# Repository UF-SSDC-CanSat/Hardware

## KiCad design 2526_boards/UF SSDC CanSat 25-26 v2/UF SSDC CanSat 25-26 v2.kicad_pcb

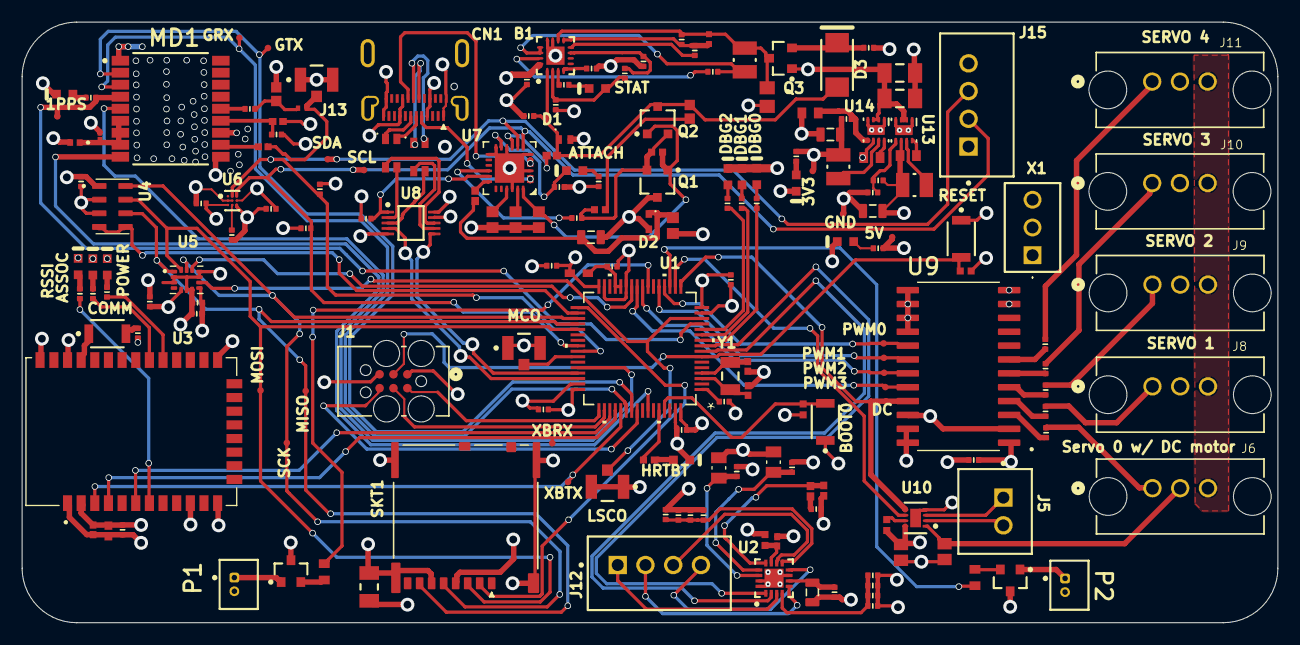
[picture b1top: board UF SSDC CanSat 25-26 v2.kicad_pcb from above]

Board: 4 copper layers, 115.0 x 55.0 mm, 170 parts (0 on the bottom side), 140 nets.

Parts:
B1: BQ25306RTER; QFN50P300X300X80_HS-17N
C1, C7, C8, C9, C14, C16, C18, C19, C21, C27, C30: Capacitor 100nF +/-20% 50V 0402; CAPC0402(1005)60_L
C2, C5, C29: GCM1555C1H9R0BA16D; CAPC1005X06N
C3: Capacitor 1 uF +/- 10% 6.3 V 1005; CAPC1005X55X25ML5T10
C4, C40: Capacitor 10µF +/-40% 6.3V 0402; CAPC0402(1005)60_L
C6: GRM0335C1H560JA01D; CAPC0603X03N
C12, C22: Capacitor 100 nF +/-10% 50 V 0603; CAPC1608X90X40NL10T20
C13: CL05C101JB5NNNC; CAPC1005X06N
C15, C20, C36, C37, C48: Capacitor 2,2µF +/-20% 10V 0402; CAPC0402(1005)60_L
C17, C50: Capacitor 10nF +/-20% 50V 0402; CAPC0402(1005)60_L
C23, C24, C25, C26: Capacitor 1uF +/- 10% 16V 0603; CAPC1608X90X35ML15T15
C28, C46: Capacitor 100 nF +/-10% 50 V 0805; CAPC2013X95X50LL10T25
C31, C33: Capacitor 10 uF +/- 10% 16 V 1206; CAPC3216X180X50NL20T25
C32, C34, C47: Capacitor 22µF +/-40% 16V 0805; CAPC0805(2012)145_L
C35: Capacitor 470pF +/-20% 50V 0402; CAPC0402(1005)60_L
C38: Capacitor 47nF +/-20% 50V 0402; CAPC0402(1005)60_L
C39: Capacitor 10 uF +/- 10% 16 V 0805; CAPC2013X135X45NL10T25
C45: Capacitor 100 uF +/- 20% 6.3 V 1206; CAPC3216X190X55LL30T25
C49: Capacitor 1nF +/-20% 50V 0402; CAPC0402(1005)33_L
C51: Capacitor 22nF +/-20% 10V 0402; CAPC0402(1005)60_L
CN1: DX07S024JJ3R1300; JAE-DX07S024JJ3_V
D1: ESDA25P35-1U1M; DFN105P160X60-2N
D2: BZT585B6V2T-7; SODFL160X65-2N
D3: SS12-TP; MCC-DO-214AC-2_V
DS1, DS5, DS7: LTW-C191TS5; LTST-LTW-C191TS5_V
DS2, DS3, DS4, DS6: LTST-C190AKT; LTST-C190AKT-2_V
DS8, DS11, DS12: LTST-C190GKT; LTST-C190GKT_V
DS9: LTST-C190KSKT; LTST-C190KSKT_V
DS10: LTST-C190KRKT; LTST-C191KRKT_V
J1: TC2030-IDC; CONN_TC2030-IDC_TGC
J2, J3, J13: U.FL-R-SMT(10); HRS-U.FL-R-SMT_V
J5: 70543-0036; FP-70543-0036-MFG
J6, J8, J9, J10, J11: 705410072; CONN_SDA-70541-xxxx_03_MOL
J12, J15: 70543-0108; FP-70543-0108-MFG
L: LQG15HS27NJ02D; INDC1005X55N
L1: LQG15HS68NJ02D; INDC1005X06N
L2: BLM18AG121SN1D; MURA-BLM18-F-H1-CHIP-2_V
L3, L4, L7: LQM2HPN2R2MG0L; INDC2520X100X60NL20T20
L5, L6: 1206USB-102MLC; DFN249P320X193-4N
MD1: TESEO-LIV3F; FP-LCC-18-MFG
P1, P2: 653002114822
Q1, Q2: AO3400A; SOT95P280X125-3N
Q3: NTR4101PT1H; SOT95P237X111-3N
Q4, Q5: MMBT4401-7-F; SOT90P240X110-3N
R1, R2, R5, R15, R16: Resistor 100k +/-1% 0402 63 mW; RESC1005X40X25ML05T05
R3, R4, R27, R29, R33, R38: Resistor 4K7 +/-1 % 0402 63 mW; RESC0402(1005)_L
R6, R45: 10R2F; RESC0402(1005)_L
R7, R8, R9, R10, R11, R12, R13, R28, R40, R47, R48: Resistor 1K +/-5 % 0402 63 mW; RESC0402(1005)_L
R14: Resistor 470R +/-5% 0805 125 mW; RESC0805(2012)_L
R17: Resistor 22K +/-1 % 0402 63 mW; RESC0402(1005)_L
R18, R19, R66: Resistor 1k +/-5% 0402 63 mW; RESC1005X40X25ML10T10
R20, R21: Resistor 4k7 +/-1% 0603 100 mW; RESC1608X55X25ML10T15
R22, R23, R24, R25, R26: Resistor 10R +/-1 % 0402 63 mW; RESC0402(1005)_L
R30, R59, R60, R61, R63, R65, R67, R69: Resistor 2R2 +/-5 % 0402 63 mW; RESC0402(1005)_L
R31, R34, R36: Resistor 100k +/-1% 0603 100 mW; RESC1608X55X25ML10T15
R32: Resistor 25K5 +/-1 % 0402 63 mW; RESC0402(1005)_L
R35: 316KR2F; RESC0402(1005)_L
R37: RC0402FR-0730KL; RESC1005X04N
R39: Resistor 1M +/-5 % 0402 63 mW; RESC0402(1005)_L
R41: Resistor 53K6 +/-1 % 0402 63 mW; RESC0402(1005)_L
R42, R43, R44: Resistor 10K +/-1 % 0402 63 mW; RESC0402(1005)_L
R46: Resistor 0R +/- 5% 0402 100 mW; RESC1005X40X25ML05T05
R49: Resistor 0R 0402 63 mW; RESC1005X40X25ML05T10
R57, R58: 0805W8F1802T5E; RESC2012X65N
R62: MC00625W0402127K; RESC1005X04N
R64: Resistor 4k7 +/-1% 0402 100 mW; RESC1005X40X25ML05T05
R68: Resistor 51k +/-5% 0402 63 mW; RESC1005X40X25ML05T10
SKT1: 5033981892; MOLX-5033981892_V
SW1, SW2, SW3: B3U-1000P; OMRON-B3U-1000_V
U1: STM32G491RCT6; LQFP_491RCT6_STM
U2: STSPIN220; QFN50P300X300X100_HS-17N
U3: XB3-24Z8UM-J; XCVR_XB3-24Z8UM-J
U4: MS560702BA03-50; SON125P300X500X100-8N
U5: ICM-42688-P; PQFN50P300X250X97-14N
U6: BMM350; FP-BMM350-IPC_C
U7: STUSB4500QTR; STM-QFN-24_V
U8: TS3USB30EDGSR; DGS0010A_L
U9: SN74LVC4245ADWR; SOIC127P1030X265-24N
U10: DRV8838DSGR; FP-DSG0008A-IPC_C
U13, U14: TPS62160DSGT; DSG0008A_V
X1: T101SHCQE
Y1: FC-135; EPSON-FC-135_V

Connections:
3V3: C1.2, C3.2, C4.2, C7.1, C8.1, C9.1, C14.1, C15.2, C16.2, C17.2, C18.2, C19.2, C28.2, C29.2, C30.2, C34.2, C45.1, C47.1, C48.1, J1.1, L.1, L2.1, L4.2, R1.1, R3.1, R4.1, R27.2, R28.2, R29.2, R34.2, R35.2, R46.2, R48.1, R49.1, R57.2, R58.2, R62.1, SKT1.4, SW2.1, U1.16, U1.32, U1.48, U1.64, U3.2, U4.1, U5.5, U5.8, U6.B3, U6.C1, U8.10, U9.23, U9.24, U10.8, U14.6
5V: C27.1, C32.2, L3.2, Q4.3, Q5.3, R31.1, R32.2, R47.1, U9.1, U13.6
+BATT: J15.1, X1.2, X1.3
BAT: B1.10, C35.2, C39.2, L7.2, Q3.3, R37.2
B_FETS: C24.2, Q1.1, Q2.1, R15.2, U7.24
CAM0: R20.1, U1.23
CAM1: R21.1, U1.19
CC1: CN1.A5, U7.1, U7.2
CC2: CN1.B5, U7.4, U7.5
CC_SELECTn: R27.1, U7.17, U8.1
CLK_32k: J3.3, U1.14, U5.9
DATA_N: U1.45, U8.6
DATA_P: U1.46, U8.4
DC.EN: U1.17, U9.21, U10.5
DC.PH: U1.18, U10.6
DISCHn: B1.1, C22.2, C36.1, D1.1, D3.1, Q2.3, R19.2
FB: B1.9, C35.1, R37.1, R38.2
FB_GND: B1.8, R38.1
GND: B1.11, B1.12, B1.17, C2.2, C3.1, C4.1, C5.2, C6.2, C7.2, C8.2, C9.2, C12.2, C14.2, C15.1, C16.1, C17.1, C18.1, C19.1, C20.2, C21.2, C23.1, C24.1, C25.1, C26.1, C27.2, C28.1, C29.1, C30.1, C31.1, C32.1, C33.1, C34.1, C36.2, C37.2, C39.1, C40.1, C45.2, C46.2, C49.1, C50.1, C51.1, CN1.A1, CN1.A12, CN1.B1, CN1.B12, D1.2, DS1.2, DS2.2, DS3.2, DS4.2, DS5.2, DS8.2, DS9.2, DS10.2, DS11.2, DS12.2, J1.5, J2.1, J2.2, J3.1, J3.2, J6.3, J8.3, J9.3, J10.3, J11.3, J13.1, J13.2, J15.4, MD1.1, MD1.10, MD1.12, P1.2, P2.2, R2.1, R30.2, R33.2, R36.2, R39.1, R41.1, R43.2, R44.2, R45.1, R59.2, R60.2, R61.2, R63.2, R64.2, R65.2, R67.2, R68.1, R69.2, SKT1.6, SKT1.11, SKT1.12, SKT1.13, SKT1.14, SW1.1, U1.15, U1.27, U1.31, U1.47, U1.63, U2.7, U2.15, U2.16, U2.17, U3.1, U3.10, U3.12, U3.21, U3.32, U3.34, U4.2, U4.3, U5.2, U5.3, U5.6, U5.7, U5.10, U5.11, U6.B1, U6.B2, U6.C3, U7.3, U7.6, U7.10, U7.12, U7.13, U7.22, U7.25, U8.5, U8.9, U9.2, U9.11, U9.12, U9.13, U9.14, U9.15, U9.16, U9.22, U10.4, U10.9, U13.1, U13.4, U13.9, U14.1, U14.4, U14.9
GPS_1PPS: MD1.4, R13.1, U1.13
GPS_RST: MD1.9, U1.58
GPS_WAKE: MD1.5, U1.44
I2C.I2C3_SCL: J15.2, R3.2, U1.40, U6.A3, U7.7
I2C.I2C3_SDA: J15.3, R4.2, U1.41, U6.A2, U7.8
NetB1_3: B1.3, R40.2
NetB1_4: B1.4, R41.2
NetB1_7: B1.7, R42.2, R43.1
NetB1_13: B1.13, B1.14, C38.2, L7.1
NetB1_15: B1.15, C38.1
NetC1_1: C1.1, U1.1
NetC2_1: C2.1, U1.4, Y1.2
NetC5_1: C5.1, U1.3, Y1.1
NetC6_1: C6.1, L.2, MD1.6, MD1.7, MD1.8
NetC12_1: C12.1, L1.1, R6.2
NetC13_1: C13.1, MD1.11
NetC13_2: C13.2, J13.3, L1.2
NetC20_1: C20.1, U6.C2
NetC21_1: C21.1, L2.2, U1.28, U1.29
NetC22_1: C22.1, R16.1
NetC23_2: C23.2, D2.1, R14.1, R18.2
NetC25_2: C25.2, U7.21
NetC26_2: C26.2, U7.23
NetC47_2: C47.2, C48.2, U2.6
NetC49_2: C49.2, R57.1, U2.14
NetC50_2: C50.2, R58.1, U2.13
NetC51_2: C51.2, R66.1
NetD3_2: D3.2, Q3.2, R39.2
NetDS1_1: DS1.1, R5.1
NetDS2_1: DS2.1, R7.1
NetDS3_1: DS3.1, R8.1
NetDS4_1: DS4.1, R9.1
NetDS5_1: DS5.1, R13.2
NetDS6_1: DS6.1, R28.1
NetDS6_2: DS6.2, R29.1, U7.11
NetDS7_2: DS7.2, R40.1
NetDS8_1: DS8.1, R10.2
NetDS9_1: DS9.1, R11.2
NetDS10_1: DS10.1, R12.2
NetDS11_1: DS11.1, R47.2
NetDS12_1: DS12.1, R48.2
NetJ1_2: J1.2, U1.49
NetJ1_3: J1.3, R1.2, SW1.2, U1.7
NetJ1_4: J1.4, U1.50
NetJ1_6: J1.6, U1.56
NetJ5_1: J5.1, U10.3
NetJ5_2: J5.2, U10.2
NetJ6_1: J6.1, R22.2
NetJ8_1: J8.1, R23.2
NetJ9_1: J9.1, R24.2
NetJ10_1: J10.1, R25.2
NetJ11_1: J11.1, R26.2
NetJ12_1: J12.1, U2.3
NetJ12_2: J12.2, U2.5
NetJ12_3: J12.3, U2.10
NetJ12_4: J12.4, U2.8
NetL3_1: L3.1, U13.7
NetL4_1: L4.1, U14.7
NetL5_2: L5.2, U8.7
NetL5_3: L5.3, U8.3
NetL6_2: L6.2, U8.8
NetL6_3: L6.3, U8.2
NetMD1_13: MD1.13, R44.1, R49.2
NetMD1_14: MD1.14, R6.1
NetP1_1: P1.1, Q4.1
NetP2_1: P2.1, Q5.1
NetQ1_2: Q1.2, Q2.2, R15.1, R16.2, R17.2
NetQ4_2: Q4.2, R20.2
NetQ5_2: Q5.2, R21.2
NetR2_2: R2.2, SW2.2, U1.61
NetR5_2: R5.2, U1.60
NetR7_2: R7.2, U1.12
NetR8_2: R8.2, U1.11
NetR9_2: R9.2, U1.10
NetR10_1: R10.1, U3.25
NetR11_1: R11.1, U3.26
NetR12_1: R12.1, U3.7
NetR17_1: R17.1, U7.16
NetR18_1: R18.1, U7.18
NetR19_1: R19.1, U7.9
NetR22_1: R22.1, U9.3
NetR23_1: R23.1, U9.4
NetR24_1: R24.1, U9.5
NetR25_1: R25.1, U9.6
NetR26_1: R26.1, U9.7
NetR30_1: R30.1, R59.1, R60.1, R61.1, U2.4
NetR31_2: R31.2, U13.8
NetR32_1: R32.1, R33.1, U13.5
NetR34_1: R34.1, U14.8
NetR35_1: R35.1, R36.1, U14.5
NetR45_2: R45.2, SW3.2
NetR46_1: R46.1, U10.7
NetR62_2: R62.2, R64.1, U2.11
NetR63_1: R63.1, R65.1, R67.1, R69.1, U2.9
NetR66_2: R66.2, R68.2, U2.12
NetSW3_1: SW3.1, U3.31
PORT_D1_N: CN1.A7, L6.1
PORT_D1_P: CN1.A6, L6.4
PORT_D2_N: CN1.B7, L5.1
PORT_D2_P: CN1.B6, L5.4
RCC_MCO: J2.3, U1.42
REGN: B1.2, C37.1, DS7.1, R42.1
SERVO.PWM0: U1.20, U9.17
SERVO.PWM1: U1.21, U9.18
SERVO.PWM2: U1.24, U9.19
SERVO.PWM3: U1.25, U9.20
SPI.BMP_nCS: U1.34, U4.4, U4.5
SPI.IMU_nCS: U1.26, U5.12
SPI.MISO: SKT1.7, U1.36, U4.6, U5.1
SPI.MOSI: SKT1.3, U1.37, U4.7, U5.14
SPI.SCK: SKT1.5, U1.35, U4.8, U5.13
SPI.SD_nCS: SKT1.2, U1.33
STEP.DIR0: U1.9, U2.1
STEP.STEP0: U1.8, U2.2
UART.GPS_RX: MD1.3, U1.54
UART.GPS_TX: MD1.2, U1.55
UART.XBEE_RX: U1.52, U3.4
UART.XBEE_TX: U1.53, U3.3
VBUS: CN1.A4, CN1.A9, CN1.B4, CN1.B9, D2.2, Q1.3, R14.2
VDC: B1.16, C31.2, C33.2, C40.2, C46.1, J6.2, J8.2, J9.2, J10.2, J11.2, Q3.1, U10.1, U13.2, U13.3, U14.2, U14.3, X1.1
XBEE_RST: U1.51, U3.6
